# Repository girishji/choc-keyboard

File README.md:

## Kailh Choc Keyboard with hotswap

A keyboard PCB for Kailh Choc low profile switches using KiCad. PCB has
soldering holes for Blackpill (STM32F401) and Adafruit IS31FL3731 breakout
board.

- Use 1.2mm thickness pcb (suitable for Choc 1350 hotswap sockets)
- Diodes are SOD-123 (1N4148)
- LED is SMD 6028 monochrome (you can get white ones from aliexpress). They are
  connected through charlieplex using IS31FL3731 LED driver (Adafruit's
  breakout board). 
- IS31FL3731 drives (PWM) LEDs at 8k Hz. This may cause audible buzz from the
  ceramic capacitors on board of Adafruit board when driven full power. To
  remove noise replace the 2 10uF capacitors on the Adafruit board with
  tantalum capacitors. Alternately, set maximum intensity of LEDs to a value of
  100 (max is 256) in QMK.
- MCU is STM32F401 (Blackpill). See the schematic for row/column connections.
  This MCU comes with USB-C.
- QMK code for this keyboard is on
  [github](https://github.com/girishji/qmk_firmware/tree/girish_dev_branch/keyboards/chockb/rev1)
- Switch plate with cutouts for switches is in switch-plate directory; If you are
  using jlcpcb, have it made with 1.2mm pcb; preferably in aluminum since it holds
  the switches better.
- There are gerber files for jlcpcb; Compress them into a zip file and upload
  it to jlcpcb

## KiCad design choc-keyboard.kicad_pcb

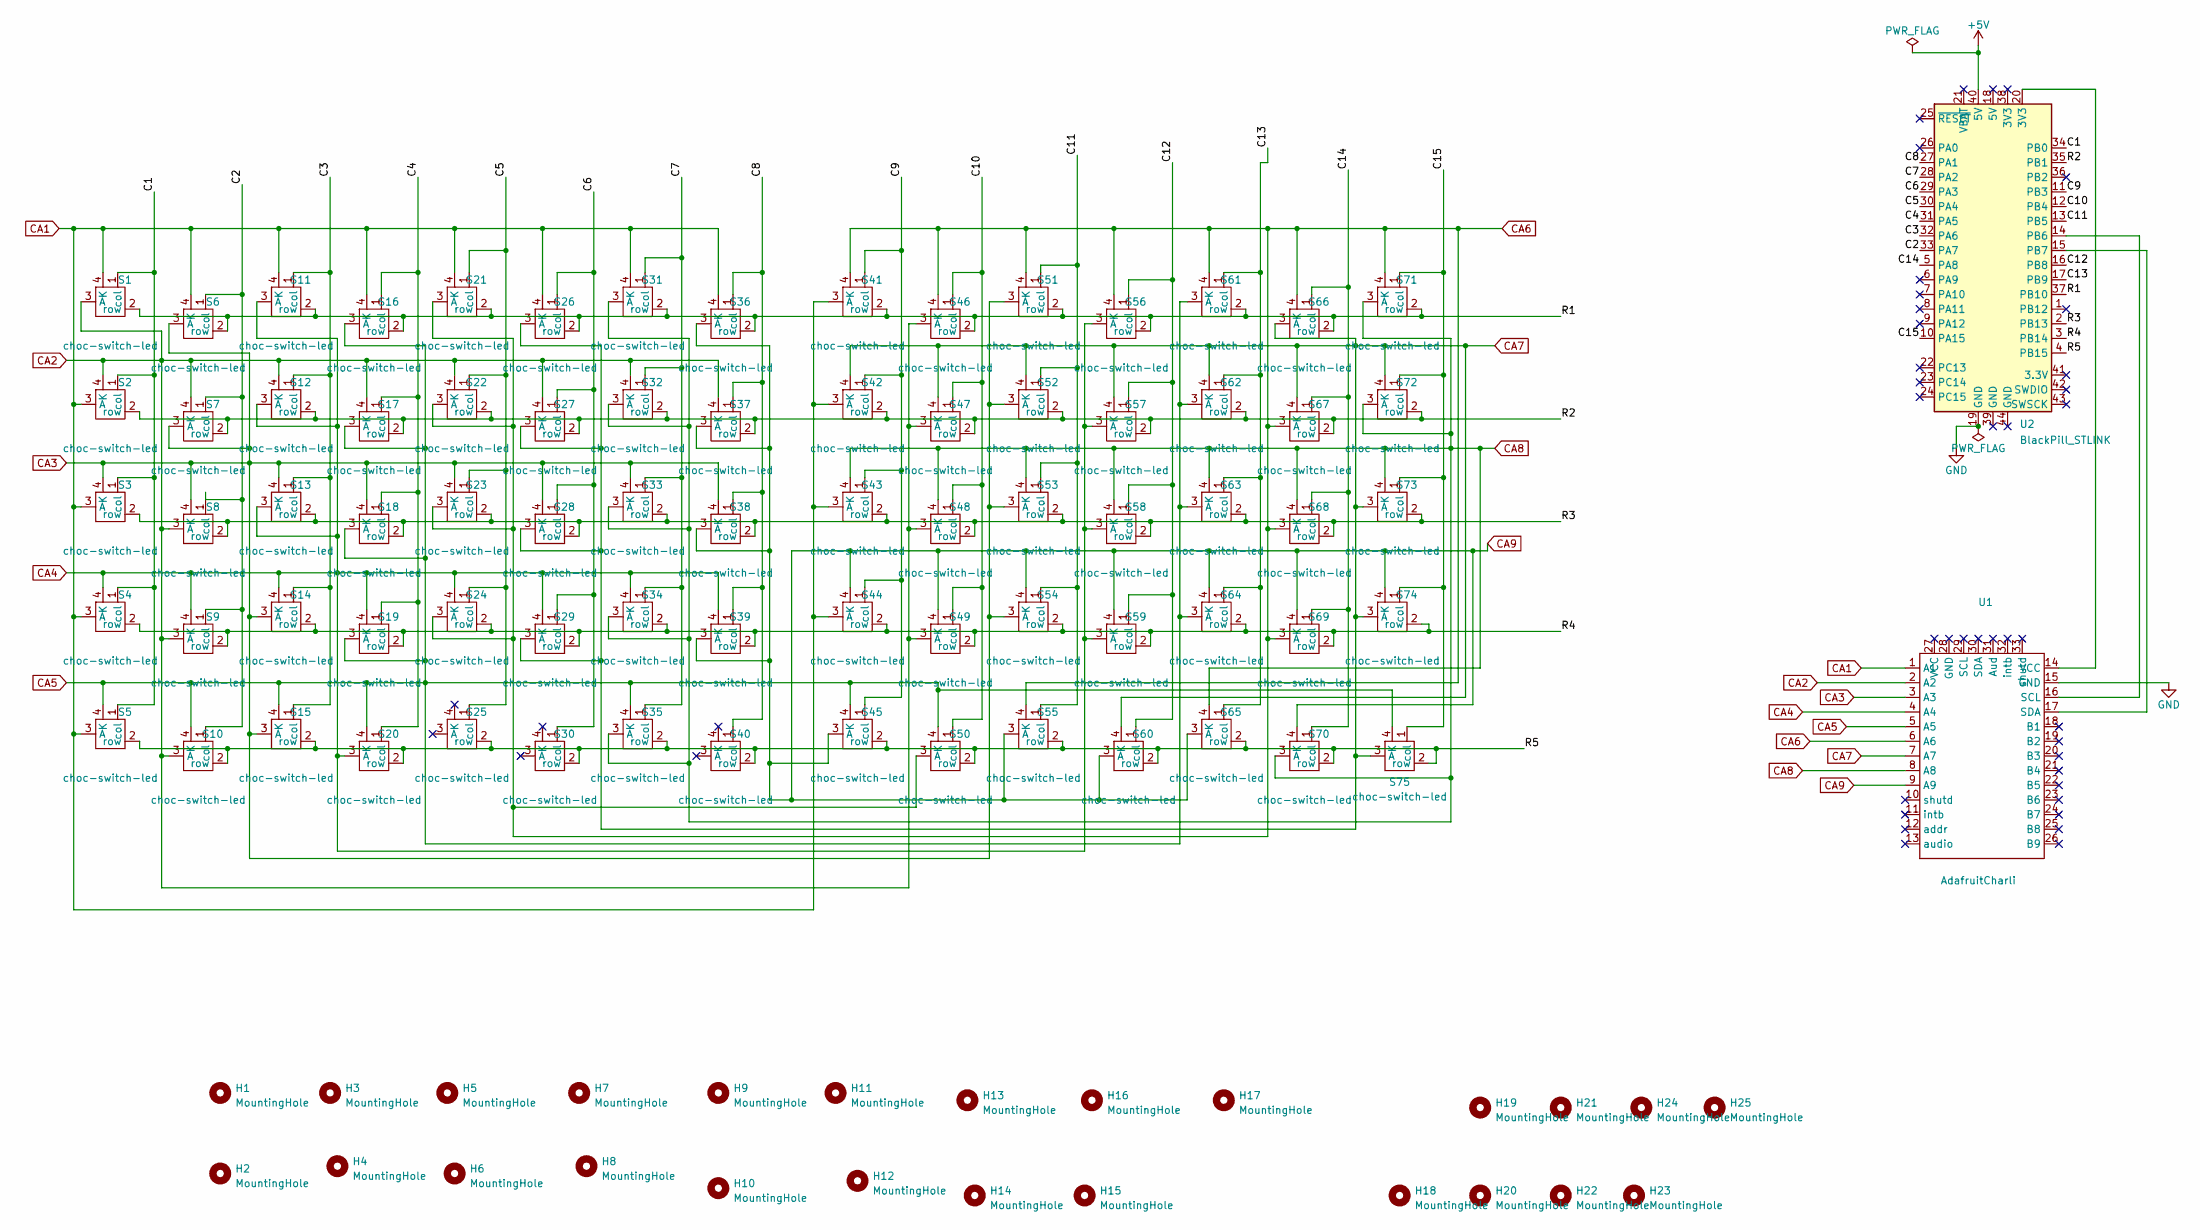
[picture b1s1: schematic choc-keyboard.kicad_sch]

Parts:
H1, H2, H3, H4, H5, H6, H7, H8, H9, H10, H11, H12, H13, H14, H15, H16, H17: MountingHole; MountingHole_2.2mm_M2_jlcpcb
H18, H19, H20, H21, H22, H23, H24, H25: MountingHole; TestPoint_Plated_Hole_D1.2mm
S1, S3, S4, S5, S6, S7, S8, S9, S10, S11, S12, S13, S14, S15, S16, S17, S18, S19, S20, S21, S22, S23, S24, S25, S26, S27, S28, S29, S30, S31, S32, S33, S34, S35, S36, S37, S38, S39, S40, S41, S42, S43, S44, S45, S46, S47, S48, S49, S50, S51, S52, S53, S54, S55, S56, S57, S58, S59, S60, S61, S62, S63, S64, S65, S66, S67, S68, S69, S70, S71, S72, S73, S74, S75: choc-switch-led; SW_Hotswap_Kailh_Choc
S2: choc-switch-led; SW_Hotswap_Kailh_Choc_noLed
U1: AdafruitCharli; AdafruitCharliplex
U2: BlackPill_STLINK

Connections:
+5V: U2.40 (5V)
/C1: S1.1 (col), S2.1 (col), S3.1 (col), S4.1 (col), S5.1 (col), U2.34 (PB0)
/C2: S6.1 (col), S7.1 (col), S8.1 (col), S9.1 (col), S10.1 (col), U2.33 (PA7)
/C3: S11.1 (col), S12.1 (col), S13.1 (col), S14.1 (col), S15.1 (col), U2.32 (PA6)
/C4: S16.1 (col), S17.1 (col), S18.1 (col), S19.1 (col), S20.1 (col), U2.31 (PA5)
/C5: S21.1 (col), S22.1 (col), S23.1 (col), S24.1 (col), S25.1 (col), U2.30 (PA4)
/C6: S26.1 (col), S27.1 (col), S28.1 (col), S29.1 (col), S30.1 (col), U2.29 (PA3)
/C7: S31.1 (col), S32.1 (col), S33.1 (col), S34.1 (col), S35.1 (col), U2.28 (PA2)
/C8: S36.1 (col), S37.1 (col), S38.1 (col), S39.1 (col), S40.1 (col), U2.27 (PA1)
/C9: S41.1 (col), S42.1 (col), S43.1 (col), S44.1 (col), S45.1 (col), U2.11 (PB3)
/C10: S46.1 (col), S47.1 (col), S48.1 (col), S49.1 (col), S50.1 (col), U2.12 (PB4)
/C11: S51.1 (col), S52.1 (col), S53.1 (col), S54.1 (col), S55.1 (col), U2.13 (PB5)
/C12: S56.1 (col), S57.1 (col), S58.1 (col), S59.1 (col), S60.1 (col), U2.16 (PB8)
/C13: S61.1 (col), S62.1 (col), S63.1 (col), S64.1 (col), S65.1 (col), U2.17 (PB9)
/C14: S66.1 (col), S67.1 (col), S68.1 (col), S69.1 (col), S70.1 (col), U2.5 (PA8)
/C15: S71.1 (col), S72.1 (col), S73.1 (col), S74.1 (col), S75.1 (col), U2.10 (PA15)
/R1: S1.2 (row), S6.2 (row), S11.2 (row), S16.2 (row), S21.2 (row), S26.2 (row), S31.2 (row), S36.2 (row), S41.2 (row), S46.2 (row), S51.2 (row), S56.2 (row), S61.2 (row), S66.2 (row), S71.2 (row), U2.37 (PB10)
/R2: S2.2 (row), S7.2 (row), S12.2 (row), S17.2 (row), S22.2 (row), S27.2 (row), S32.2 (row), S37.2 (row), S42.2 (row), S47.2 (row), S52.2 (row), S57.2 (row), S62.2 (row), S67.2 (row), S72.2 (row), U2.35 (PB1)
/R3: S3.2 (row), S8.2 (row), S13.2 (row), S18.2 (row), S23.2 (row), S28.2 (row), S33.2 (row), S38.2 (row), S43.2 (row), S48.2 (row), S53.2 (row), S58.2 (row), S63.2 (row), S68.2 (row), S73.2 (row), U2.2 (PB13)
/R4: S4.2 (row), S9.2 (row), S14.2 (row), S19.2 (row), S24.2 (row), S29.2 (row), S34.2 (row), S39.2 (row), S44.2 (row), S49.2 (row), S54.2 (row), S59.2 (row), S64.2 (row), S69.2 (row), S74.2 (row), U2.3 (PB14)
/R5: S5.2 (row), S10.2 (row), S15.2 (row), S20.2 (row), S25.2 (row), S30.2 (row), S35.2 (row), S40.2 (row), S45.2 (row), S50.2 (row), S55.2 (row), S60.2 (row), S65.2 (row), S70.2 (row), S75.2 (row), U2.4 (PB15)
CA1: S1.4 (K), S2.3 (A), S3.3 (A), S4.3 (A), S5.3 (A), S6.4 (K), S11.4 (K), S16.4 (K), S21.4 (K), S26.4 (K), S31.4 (K), S36.4 (K), S41.3 (A), S42.3 (A), S43.3 (A), S44.3 (A), U1.1 (A1)
CA2: S1.3 (A), S2.4 (K), S7.4 (K), S8.3 (A), S9.3 (A), S10.3 (A), S12.4 (K), S17.4 (K), S22.4 (K), S27.4 (K), S32.4 (K), S37.4 (K), S46.3 (A), S47.3 (A), S48.3 (A), S49.3 (A), U1.2 (A2)
CA3: S3.4 (K), S6.3 (A), S7.3 (A), S8.4 (K), S13.4 (K), S14.3 (A), S15.3 (A), S18.4 (K), S23.4 (K), S28.4 (K), S33.4 (K), S38.4 (K), S51.3 (A), S52.3 (A), S53.3 (A), S54.3 (A), U1.3 (A3)
CA4: S4.4 (K), S9.4 (K), S11.3 (A), S12.3 (A), S13.3 (A), S14.4 (K), S19.4 (K), S20.3 (A), S24.4 (K), S29.4 (K), S34.4 (K), S39.4 (K), S56.3 (A), S57.3 (A), S58.3 (A), S59.3 (A), U1.4 (A4)
CA5: S5.4 (K), S10.4 (K), S15.4 (K), S16.3 (A), S17.3 (A), S18.3 (A), S19.3 (A), S20.4 (K), S35.4 (K), S45.4 (K), S50.4 (K), S61.3 (A), S62.3 (A), S63.3 (A), S64.3 (A), S75.4 (K), U1.5 (A5)
CA6: S21.3 (A), S22.3 (A), S23.3 (A), S24.3 (A), S41.4 (K), S46.4 (K), S50.3 (A), S51.4 (K), S55.4 (K), S56.4 (K), S61.4 (K), S66.4 (K), S67.3 (A), S68.3 (A), S69.3 (A), S71.4 (K), U1.6 (A6)
CA7: S26.3 (A), S27.3 (A), S28.3 (A), S29.3 (A), S42.4 (K), S47.4 (K), S52.4 (K), S57.4 (K), S60.4 (K), S62.4 (K), S66.3 (A), S67.4 (K), S72.4 (K), S73.3 (A), S74.3 (A), S75.3 (A), U1.7 (A7)
CA8: S31.3 (A), S32.3 (A), S33.3 (A), S34.3 (A), S35.3 (A), S43.4 (K), S48.4 (K), S53.4 (K), S58.4 (K), S63.4 (K), S65.4 (K), S68.4 (K), S70.3 (A), S71.3 (A), S72.3 (A), S73.4 (K), U1.8 (A8)
CA9: S36.3 (A), S37.3 (A), S38.3 (A), S39.3 (A), S44.4 (K), S45.3 (A), S49.4 (K), S54.4 (K), S55.3 (A), S59.4 (K), S60.3 (A), S64.4 (K), S65.3 (A), S69.4 (K), S70.4 (K), S74.4 (K), U1.9 (A9)
GND: U1.15 (GND), U2.19 (GND)
unnamed: U1.14 (VCC), U2.20 (3V3)
unnamed: U1.16 (SCL), U2.14 (PB6)
unnamed: U1.17 (SDA), U2.15 (PB7)

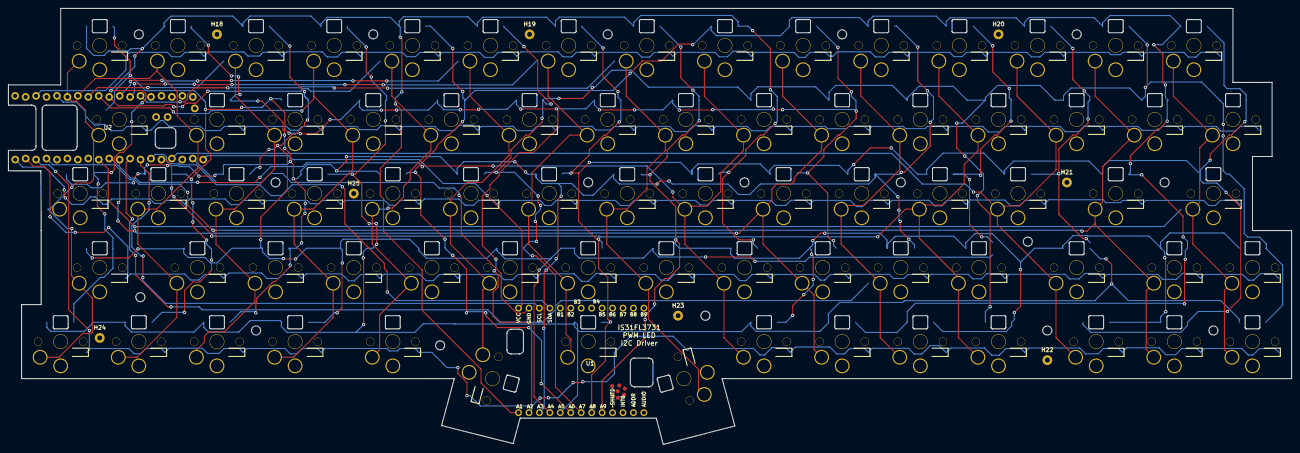
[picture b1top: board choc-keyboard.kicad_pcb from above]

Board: 2 copper layers, 311.9 x 106.0 mm, 102 parts (0 on the bottom side), 33 nets.

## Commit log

2022-07-14 First commit
    M .gitignore
    M README.md
    A choc-keyboard.kicad_pcb
    A choc-keyboard.kicad_prl
    A choc-keyboard.kicad_pro
    A choc-keyboard.kicad_sch
2022-07-21 updated footprints
    M .gitignore
    M choc-keyboard.kicad_pcb
    M choc-keyboard.kicad_prl
    M choc-keyboard.kicad_pro
    M choc-keyboard.kicad_sch
    M placesw.py
2022-08-05 Add gerber files
    M .gitignore
    M README.md
    M choc-keyboard.kicad_pro
    A jlcpcb/gerber/choc-keyboard-B_Cu.gbl
    A jlcpcb/gerber/choc-keyboard-B_Mask.gbs
    A jlcpcb/gerber/choc-keyboard-B_Paste.gbp
2022-08-05 Add images
    M README.md
